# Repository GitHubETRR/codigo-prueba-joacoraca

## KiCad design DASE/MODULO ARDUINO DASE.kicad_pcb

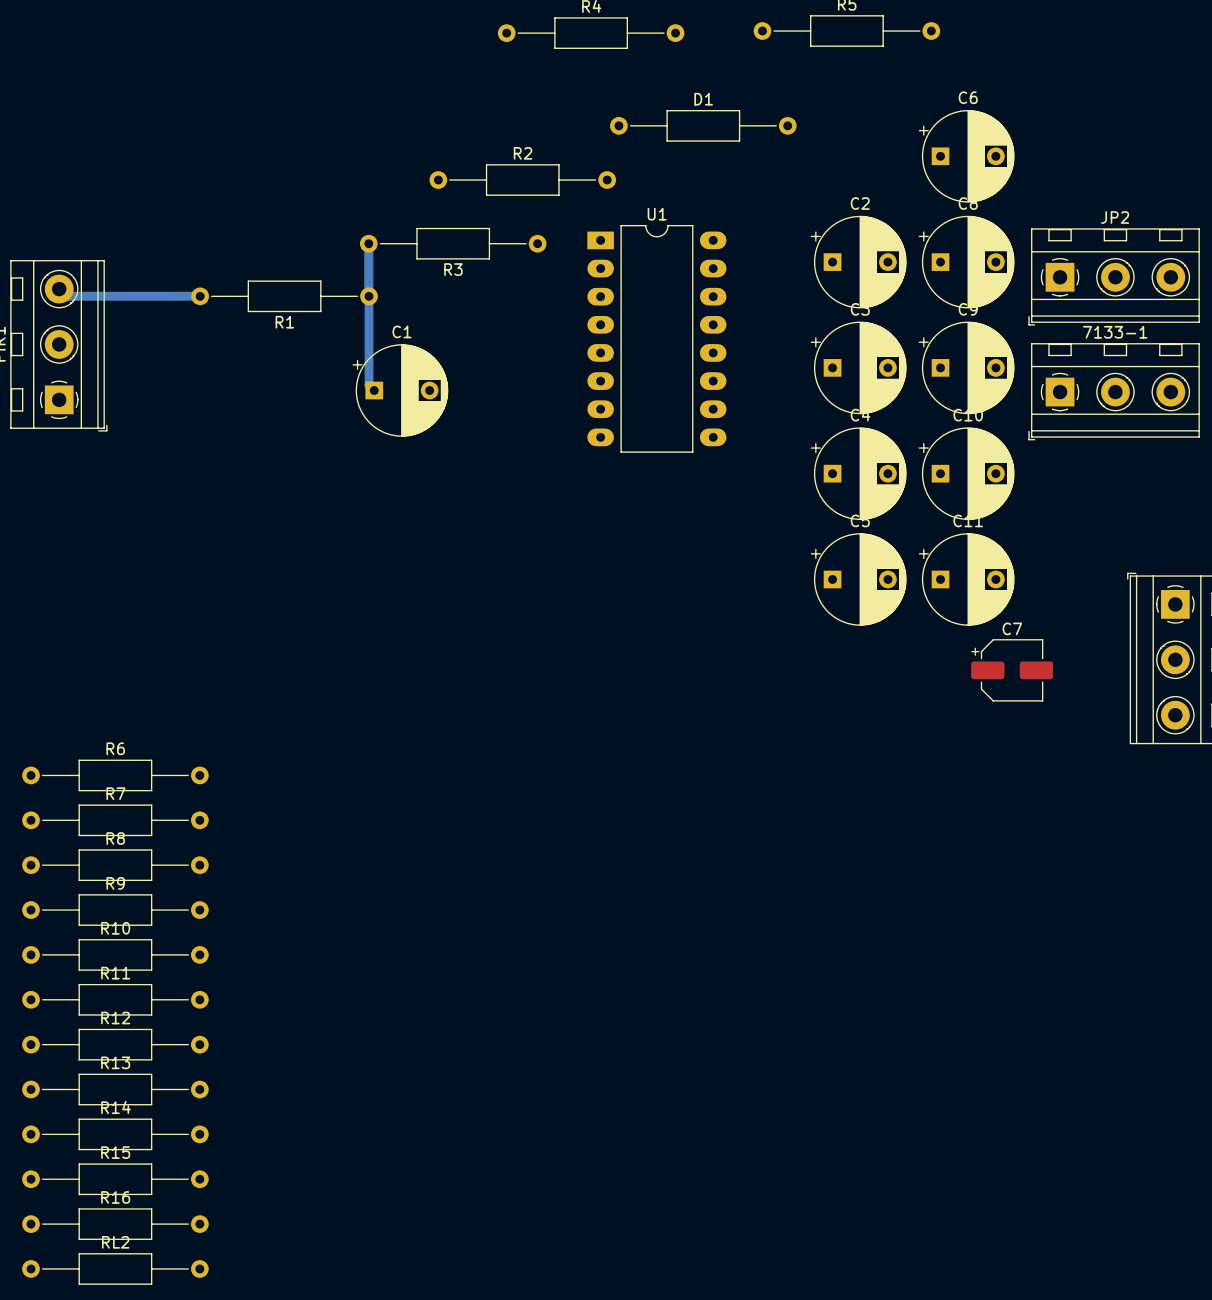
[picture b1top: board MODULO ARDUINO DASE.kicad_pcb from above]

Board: 2 copper layers, 34 parts (0 on the bottom side), 28 nets.

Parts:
7133-1: Screw_Terminal_01x03; TerminalBlock_MetzConnect_Type094_RT03503HBLU_1x03_P5.00mm_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
C1, C5: 47UF; CP_Radial_D8.0mm_P5.00mm
C2, C3, C6, C10: 103P; CP_Radial_D8.0mm_P5.00mm
C4: 502P; CP_Radial_D8.0mm_P5.00mm
C7: 104P; CP_Elec_5x3
C8: 22uf; CP_Radial_D8.0mm_P5.00mm
C9: 103p; CP_Radial_D8.0mm_P5.00mm
C11: 104P; CP_Radial_D8.0mm_P5.00mm
D1: D; R_Axial_DIN0207_L6.3mm_D2.5mm_P15.24mm_Horizontal
JP1, JP2: Screw_Terminal_01x03; TerminalBlock_MetzConnect_Type094_RT03503HBLU_1x03_P5.00mm_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
PIR1: Screw_Terminal_01x03; TerminalBlock_MetzConnect_Type094_RT03503HBLU_1x03_P5.00mm_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
R1, R6, R8: 18K; R_Axial_DIN0207_L6.3mm_D2.5mm_P15.24mm_Horizontal
R2: A9050; R_Axial_DIN0207_L6.3mm_D2.5mm_P15.24mm_Horizontal
R3: 10k; R_Axial_DIN0207_L6.3mm_D2.5mm_P15.24mm_Horizontal
R4: 47k; R_Axial_DIN0207_L6.3mm_D2.5mm_P15.24mm_Horizontal
R5, R7, R12, R13, R15: 1M; R_Axial_DIN0207_L6.3mm_D2.5mm_P15.24mm_Horizontal
R9: 470K; R_Axial_DIN0207_L6.3mm_D2.5mm_P15.24mm_Horizontal
R10: 6.8K; R_Axial_DIN0207_L6.3mm_D2.5mm_P15.24mm_Horizontal
R11: 2K; R_Axial_DIN0207_L6.3mm_D2.5mm_P15.24mm_Horizontal
R14: 10K; R_Axial_DIN0207_L6.3mm_D2.5mm_P15.24mm_Horizontal
R16: 1K; R_Axial_DIN0207_L6.3mm_D2.5mm_P15.24mm_Horizontal
RL2: 1M; R_Axial_DIN0207_L6.3mm_D2.5mm_P15.24mm_Horizontal
U1: DIP-16_W10.16mm_LongPads

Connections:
GND: C1.2, C2.2, C3.2, C5.1, C10.2, C11.2, JP1.3, PIR1.1, R2.2, R4.2, R5.2, U1.7 (VSS)
unnamed: 7133-1.1, JP1.1, R3.1, U1.8 (VRE/R), U1.11 (VCC)
unnamed: 7133-1.2, D1.1 (K)
unnamed: 7133-1.3, C11.1, JP2.3, R13.2, U1.5 (ENC)
unnamed: C1.1, R1.1, R3.2
unnamed: C3.1, C4.2
unnamed: C5.2, R6.1
unnamed: C7.1, C8.1, R11.1
unnamed: C7.2, R10.1, R11.2
unnamed: D1.2 (A), JP2.1
unnamed: JP1.2, U1.1 (A)
unnamed: JP2.2, R16.2
unnamed: C2.1, PIR1.2, R4.1, R8.1
unnamed: PIR1.3, R1.2
unnamed: R2.1, R7.2
unnamed: R9.2, RL2.1
unnamed: R14.2, R15.1
unnamed: R8.2, U1.14 (1+)
unnamed: C4.1, C9.2, R6.2, R12.2, U1.15 (1-)
unnamed: C8.2, C9.1, R12.1, U1.16 (1O)
unnamed: C6.1, R9.1, R10.2, U1.13 (2+)
unnamed: C6.2, RL2.2, U1.12 (2O)
unnamed: R5.1, U1.10 (AFI)
unnamed: R13.1, U1.6 (ENR)
unnamed: R7.1, U1.9 (INH)
unnamed: R16.1, U1.2 (OUT)
unnamed: C10.1, R15.2, U1.4 (TC)
unnamed: R14.1, U1.3 (TR)

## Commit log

2024-05-17 GitHub Classroom Feedback
2024-05-17 Setting up GitHub Classroom Feedback
2024-05-17 add online IDE url; add deadline
2024-05-17 primer codigo
2024-05-17 TP1
    Pasaje de sistemas de unidades y operaciones.
2024-05-17 Create Documentos
2024-05-17 Create Documentos
    Carpeta de documentos de Word, PDF, PowerPoint, etc.
2024-05-17 Create l
2024-05-17 TP1
    Trabajo practico sobre pasaje de unidades y operaciones de suma y resta.
2024-05-17 TP 2
    Diagramas de flujo en Pseint.
2024-05-17 Punto 1, 2 y 3
2024-05-17 TP 2
    Punto 1, 2 y 3
2024-05-17 TP 2
    Punto 4 y 5
2024-05-17 segundo commit
2024-06-04 lenguajes
2024-06-04 ejercicio 14
2024-06-05 ejercicio 15
2024-06-05 calculadora de area
2024-06-07 mover a codigos
2024-06-14 ejercicio 19
2024-11-19 Create DASE
2025-03-06 Create LE2
